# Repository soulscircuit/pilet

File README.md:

# pilet
this repository contains 3d files, pcb files, schematics, and documentation for pilet mini-computer. 
all files will be gradually released here. The schematics and pcbs are designed in kicad and released under CERN-OHL-P license. 

# current releases
- nvme module

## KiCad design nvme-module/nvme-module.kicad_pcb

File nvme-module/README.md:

#  License
The hardware design files for the Pilet PCB are licensed under the [CERN Open Hardware License v2 - Permissive (CERN-OHL-P-2.0)](https://ohwr.org/project/cernohl).

You are free to use, modify, manufacture, and sell the hardware, provided that:
- You include attribution to the original author Soulscircuit.com
- You include a copy of this license in your distribution

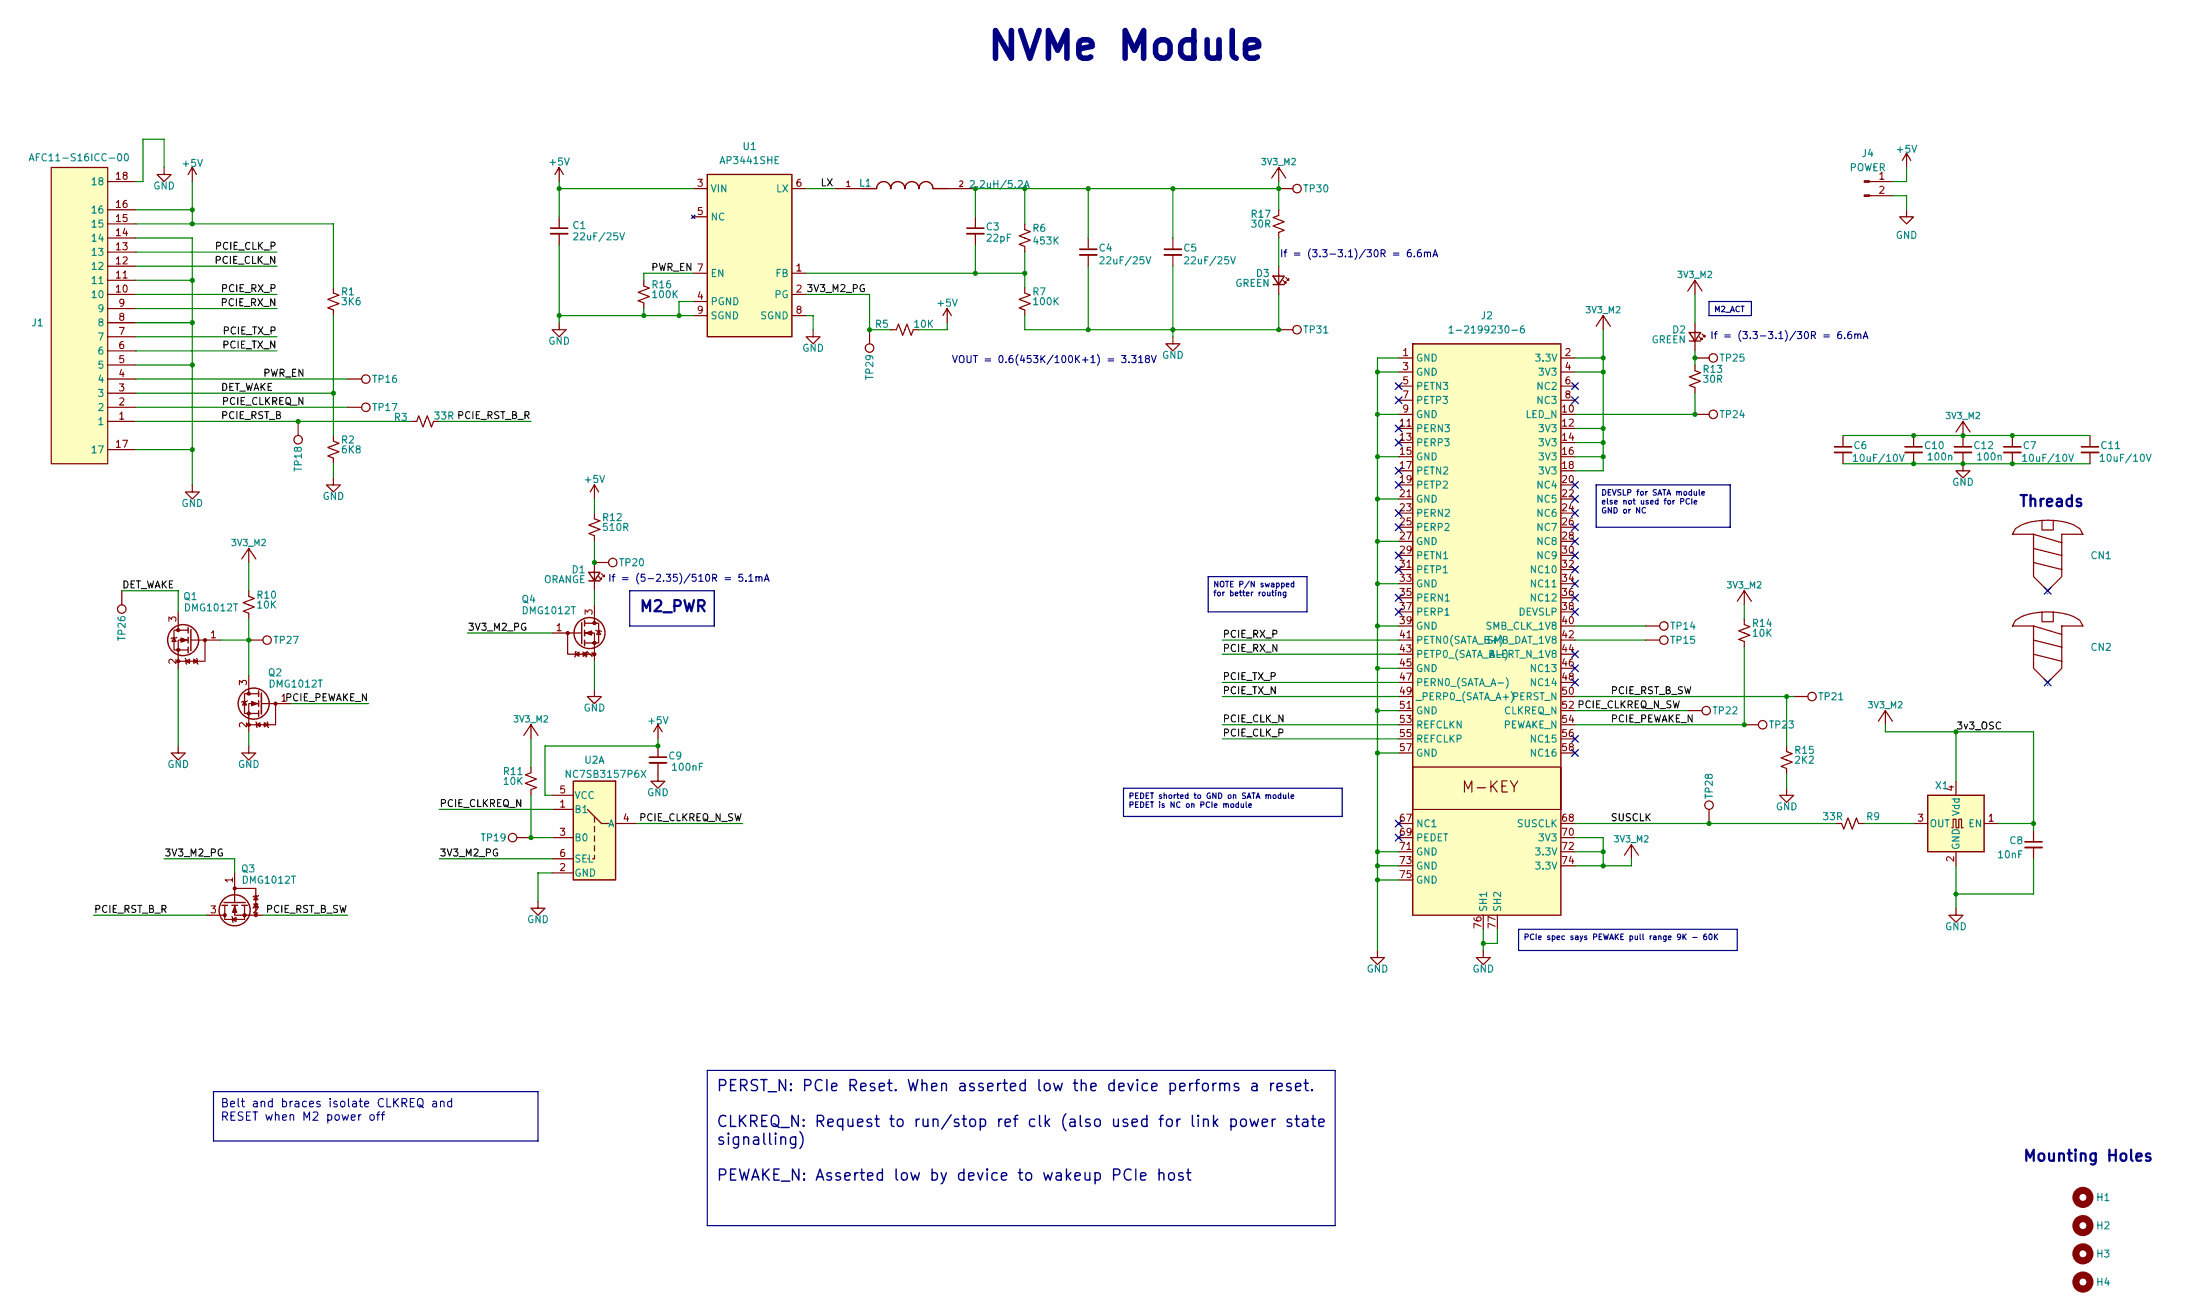
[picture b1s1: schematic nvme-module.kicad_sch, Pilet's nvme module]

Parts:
C1, C4, C5: 22uF/25V; C_0805_2012Metric; LCSC Part Number C45783
C3: 22pF; C_0603_1608Metric; LCSC Part Number C1653
C6, C7, C11: 10uF/10V; C_0603_1608Metric; LCSC Part Number C19702
C8: 10nF; C_0603_1608Metric; LCSC Part Number C57112
C9: 100nF; C_0603_1608Metric; LCSC Part Number C14663
C10, C12: 100n; C_0603_1608Metric; LCSC Part Number C14663
CN1, CN2: MountingHole_2mm
D1: ORANGE; LED_0603_1608Metric; LCSC Part Number C401119
D2, D3: GREEN; LED_0603_1608Metric; LCSC Part Number C12065
H1, H2, H3, H4: MountingHole; MountingHole_2.5mm_Pad_TopBottom
J1: AFC11-S16ICC-00; FPC-SMD_16P-L13.5-W2.0-P0.50; LCSC Part Number C11071
J2: 1-2199230-6; AMPHENOL_MDT320M03001; LCSC Part Number C4710843
J4: POWER; PinHeader_1x02_P2.54mm_Vertical; LCSC Part Number C124375
L1: 2.2uH/5.2A; IND-SMD_L5.4-W5.2_0518CDMCCDS; LCSC Part Number C212256
Q1, Q2, Q3, Q4: DMG1012T; SOT-523; LCSC Part Number C20512
R1: 3K6; R_0603_1608Metric; LCSC Part Number C22980
R2: 6K8; R_0603_1608Metric; LCSC Part Number C23212
R3, R9: 33R; R_0603_1608Metric; LCSC Part Number C23140
R5, R10, R11, R14: 10K; R_0603_1608Metric; LCSC Part Number C25804
R6: 453K; R_0603_1608Metric; LCSC Part Number C3013202
R7, R16: 100K; R_0603_1608Metric; LCSC Part Number C25803
R12: 510R; R_0603_1608Metric; LCSC Part Number C23193
R13, R17: 30R; R_0603_1608Metric; LCSC Part Number C22985
R15: 2K2; R_0603_1608Metric; LCSC Part Number C4190
TP14, TP15, TP16, TP17, TP18, TP19, TP20, TP21, TP22, TP23, TP24, TP25, TP26, TP27, TP28, TP29, TP30, TP31: TestPoint; TestPoint_Pad_D1.0mm
U1: AP3441SHE; DFN-8-1EP_2x2mm_P0.5mm_EP0.9x1.7mm; LCSC Part Number C2070918
U2: NC7SB3157P6X; SOT-363_SC-70-6; LCSC Part Number C20417168
X1: ASE-xxxMHz; OSC-SMD_4P-L3.2-W2.5-BL-1; LCSC Part Number C2650753

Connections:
3V3_M2: C3.1, C4.1, C5.1, C6.1, C7.1, C8.1, C10.1, C11.1, C12.1, D2.2 (A), J2.2 (3.3V), J2.4 (3V3), J2.12 (3V3), J2.14 (3V3), J2.16 (3V3), J2.18 (3V3), J2.70 (3V3), J2.72 (3.3V), J2.74 (3.3V), L1.2, R6.1, R10.1, R11.1, R14.1, R17.1, TP30.1, X1.1 (EN), X1.4 (Vdd)
+5V: C1.1, C9.1, J1.15, J1.16, J4.1, R1.1, R5.2, R12.1, U1.3 (VIN), U2.5 (VCC)
/3V3_M2_PG: Q3.1 (G), Q4.1 (G), R5.1, TP29.1, U1.2 (PG), U2.6 (SEL)
/ PCIE_CLKREQ_N_SW: J2.52 (CLKREQ_N), TP22.1, U2.4 (A)
/DET_WAKE: J1.3, Q1.3 (D), R1.2, R2.1, TP26.1
/LX: L1.1, U1.6 (LX)
/PCIE_CLKREQ_N: J1.2, TP17.1, U2.1 (B1)
/PCIE_CLK_N: J1.12, J2.53 (REFCLKN)
/PCIE_CLK_P: J1.13, J2.55 (REFCLKP)
/PCIE_PEWAKE_N: J2.54 (PEWAKE_N), Q2.1 (G), R14.2, TP23.1
/PCIE_RST_B: J1.1, R3.1, TP18.1
/PCIE_RST_B_R: Q3.3 (D), R3.2
/PCIE_RST_B_SW: J2.50 (PERST_N), Q3.2 (S), R15.1, TP21.1
/PCIE_RX_N: J1.9, J2.43 (PETP0_(SATA_B-))
/PCIE_RX_P: J1.10, J2.41 (PETN0(SATA_B+))
/PCIE_TX_N: J1.6, J2.49 (_PERP0_(SATA_A+))
/PCIE_TX_P: J1.7, J2.47 (PERN0_(SATA_A-))
/PWR_EN: J1.4, R16.1, TP16.1, U1.7 (EN)
/SUSCLK: J2.68 (SUSCLK), R9.2, TP28.1
GND: C1.2, C4.2, C5.2, C6.2, C7.2, C8.2, C9.2, C10.2, C11.2, C12.2, D3.1 (K), J1.5, J1.8, J1.11, J1.14, J1.17, J1.18, J2.1 (GND), J2.3 (GND), J2.9 (GND), J2.15 (GND), J2.21 (GND), J2.27 (GND), J2.33 (GND), J2.39 (GND), J2.45 (GND), J2.51 (GND), J2.57 (GND), J2.71 (GND), J2.73 (GND), J2.75 (GND), J2.76 (SH1), J2.77 (SH2), J4.2, Q1.2 (S), Q2.2 (S), Q4.2 (S), R2.2, R7.2, R15.2, R16.2, TP31.1, U1.4 (PGND), U1.8 (SGND), U1.9 (SGND), U2.2 (GND), X1.2 (GND)
unnamed: D1.2 (A), R12.2, TP20.1
unnamed: D1.1 (K), Q4.3 (D)
unnamed: D2.1 (K), R13.1, TP25.1
unnamed: D3.2 (A), R17.2
unnamed: J2.10 (LED_N), R13.2, TP24.1
unnamed: J2.40 (SMB_CLK_1V8), TP14.1
unnamed: J2.42 (SMB_DAT_1V8), TP15.1
unnamed: Q1.1 (G), Q2.3 (D), R10.2, TP27.1
unnamed: C3.2, R6.2, R7.1, U1.1 (FB)
unnamed: R11.2, TP19.1, U2.3 (B0)
unnamed: R9.1, X1.3 (OUT)

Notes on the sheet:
If = (3.3-3.1)/30R = 6.6mA
If = (5-2.35)/510R = 5.1mA
VOUT = 0.6(453K/100K+1) = 3.318V
Threads
NVMe Module
Mounting Holes
M2_ACT
PCIe spec says PEWAKE pull range 9K - 60K
M2_PWR
DEVSLP for SATA module else not used for PCIe GND or NC
PEDET shorted to GND on SATA module PEDET is NC on PCIe module
Belt and braces isolate CLKREQ and RESET when M2 power off
PERST_N: PCIe Reset. When asserted low the device performs a reset. CLKREQ_N: Request to run/stop ref clk (also used for link power state signalling) PEWAKE_N: Asserted low by device to wakeup PCIe host
NOTE P/N swapped for better routing

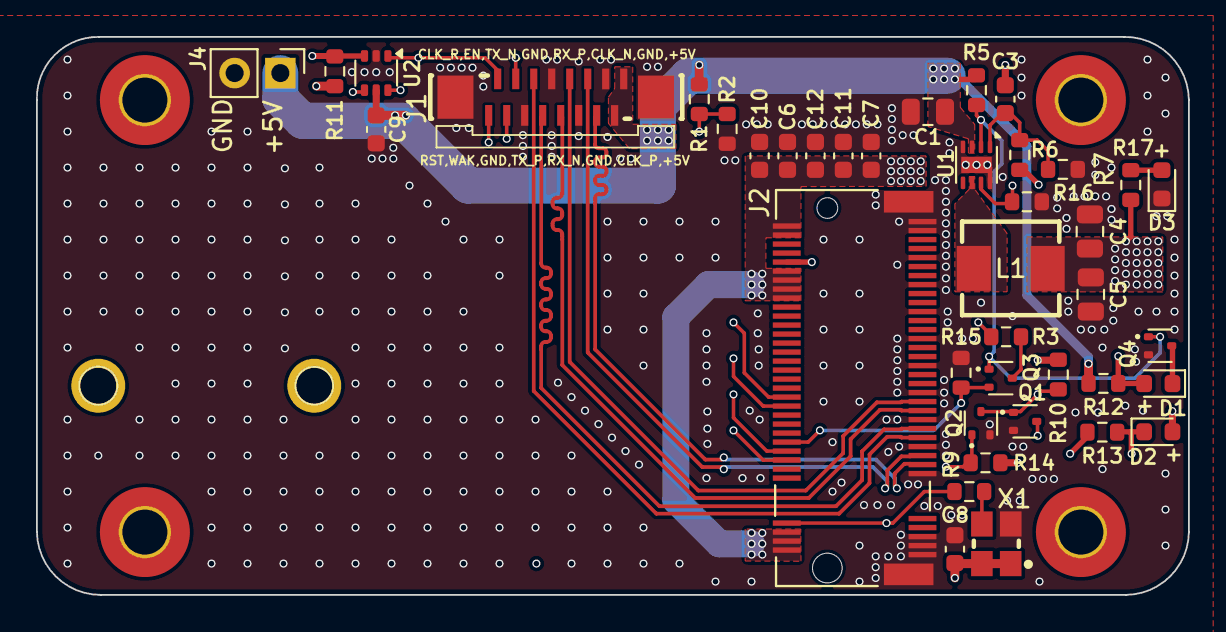
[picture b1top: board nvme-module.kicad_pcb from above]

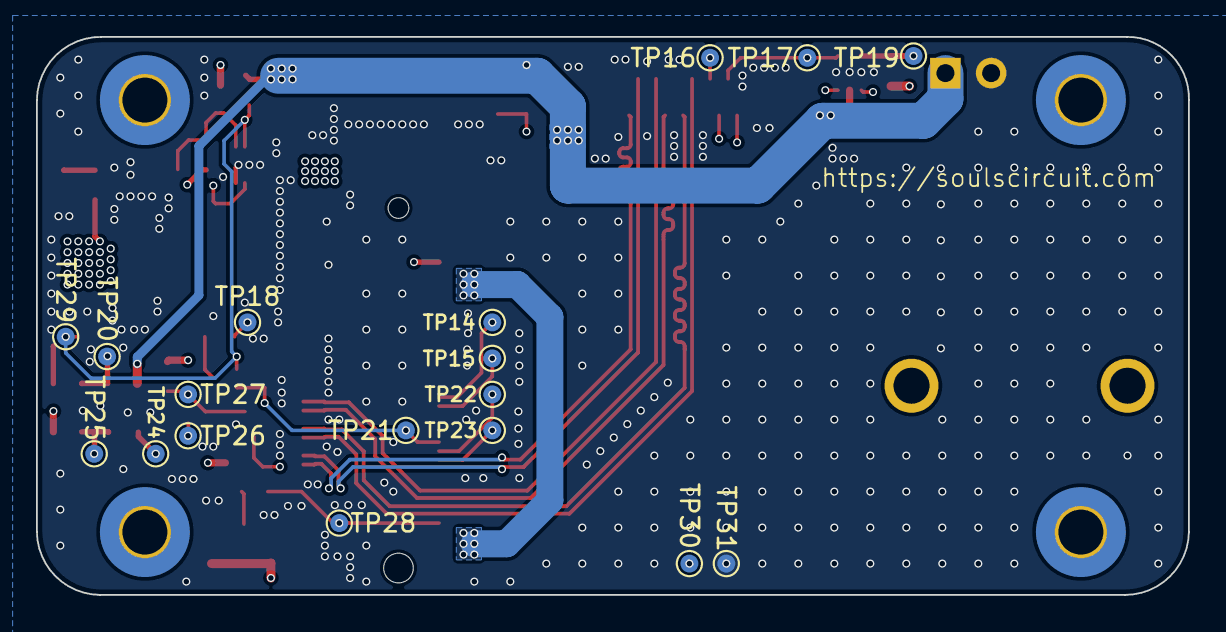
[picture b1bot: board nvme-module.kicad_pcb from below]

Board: 4 copper layers, 64.0 x 31.0 mm, 64 parts (18 on the bottom side), 31 nets.

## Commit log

2024-11-28 Create README.md
    Creating README
2024-11-28 Update README.md
    Update README
2024-12-23 Update README.md
    acknowledgments
2025-11-07 nvme module release
2025-11-07 fix nvme sub-module
